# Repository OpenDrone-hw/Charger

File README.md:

# Charger

A distributed USB-C charging system for FPV battery packs. Two boards sharing
one charge, sense and balance core: a headless **charger node** that lives with
the pack, and a **manager** hub with a display and an encoder that drives
several nodes. No design exists yet; this page is the specification. If you
want to design it, say so on [Discord](https://discord.gg/v3sWmTcx3R).

## Why

Field charging is one parallel board, one power supply and a lot of trust. The
distributed shape puts the charge controller with the pack instead: each node
does its own constant-current, constant-voltage and balancing, and the manager
becomes a user interface and a power budget rather than the thing doing the
charging. A failure is then one pack rather than the whole board.

USB-C PD is the input because it is the supply people already carry.

## Specifications

Targets, not measurements. The site imports this table once a board exists.

| | |
|---|---|
| Charger node | Headless, 2S to 6S, one per pack |
| Manager | 2S to 8S, display and encoder, drives several nodes |
| Input | USB-C PD |
| Charge controller | TI BQ25758 buck-boost, or a justified alternative |
| Balancing | Per cell |
| Chemistries | LiPo, LiHV, Li-ion, LiFe |

## Constraints

- Two boards, one shared charge, sense and balance core.
- USB-C PD input on both boards; the manager may add other inputs.
- Assembly house chosen per release. LCSC basic parts preferred. Fab-ready manufacturing files are kept in a private Incutec production repository and are not published.
- Project-local KiCad libraries only, on the org template.
- Safety first: pack fault, thermal event and mid-charge disconnect are
  designed before the UI is.

## Prior art

An earlier schematic pass (BQ25758 core, TLA2528 cell ADC, TCA9554A driving
per-cell bleed FETs, ESP32 modules for ESP-NOW between manager and nodes) was
reviewed as not functional and removed from `main` on 2026-08-13. It is
reference for the thinking, not a design to continue from: tag
`pre-reset-2026-08-13`.

## Design questions

Open questions for the design:

- How the manager and nodes talk: wired bus, and which one? This decides
  the connector and half the enclosure. The earlier pass assumed ESP-NOW.
- Power budget: how is a fixed USB-C PD budget divided across nodes that
  each want it, and who decides?
- Cell count split: the node is 2S-6S and the manager 2S-8S. Is that split
  right, or should they match?
- Safety: what happens on a pack fault, a thermal event, or a disconnect
  mid-charge. This is the only product in the line that can start a fire on
  purpose.
- Enclosure: mechanical is as much of this product as the PCB.

## In the line

What pairs with what, and what is available:
[opendrone.be](https://opendrone.be).

## Contributing

KiCad files cannot be merged, so say what you intend to change before you do,
on [Discord](https://discord.gg/v3sWmTcx3R). How everything works:
[CONTRIBUTING.md](CONTRIBUTING.md).

## License

Hardware licensed under [CERN-OHL-S-2.0](https://ohwr.org/cern_ohl_s_v2.txt),
see [LICENSE](LICENSE).

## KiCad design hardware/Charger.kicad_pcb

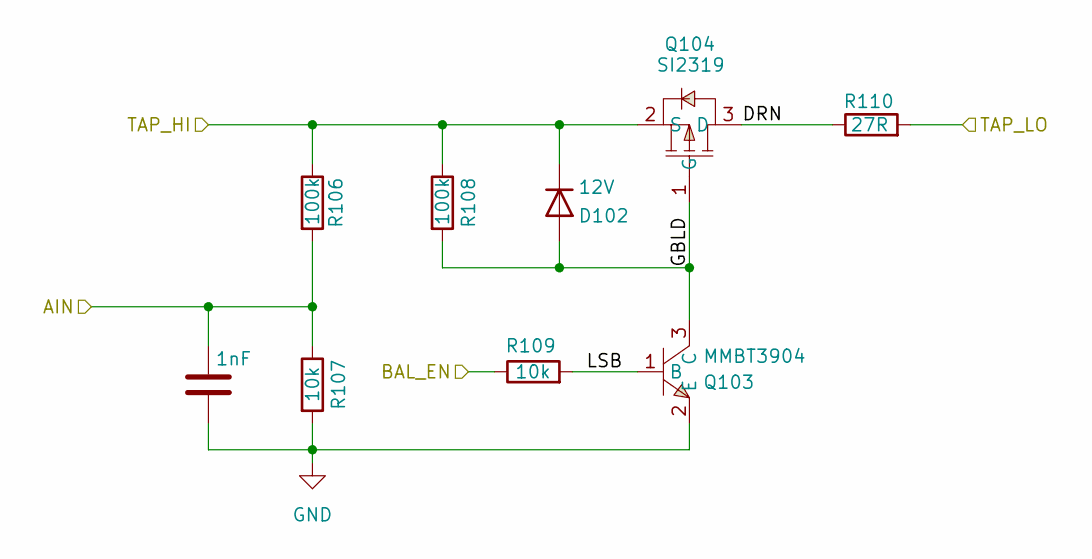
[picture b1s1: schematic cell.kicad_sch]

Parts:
C102: 1nF; C_0402_1005Metric; MPN GRM1555C1H102JA01D; LCSC C76947
D102: 12V; D_SOD-123; MPN MMSZ5242BT1G; LCSC C82050
Q103: MMBT3904; SOT-23; MPN MMBT3904; LCSC C20526
Q104: SI2319; SOT-23; MPN SI2319CDS-JSM; LCSC C18191323
R106: 100k; R_0402_1005Metric; MPN RT0402BRD07100KL; LCSC C852472
R107: 10k; R_0402_1005Metric; MPN RT0402BRD0710KL; LCSC C190095
R108: 100k; R_0402_1005Metric; MPN 0402WGF1003TCE; LCSC C25741
R109: 10k; R_0402_1005Metric; MPN 0402WGF1002TCE; LCSC C25744
R110: 27R; R_2512_6332Metric; MPN RC2512FK-7W27RL; LCSC C7337013

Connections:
/cell1/DRN: Q104.3 (D), R110.1
/cell1/GBLD: D102.2 (A), Q103.3 (C), Q104.1 (G), R108.2
/cell1/LSB: Q103.1 (B), R109.2
AIN1: C102.1, R106.2, R107.1; also elsewhere on the board
BAL_EN1: R109.1; also elsewhere on the board
GND: C102.2, Q103.2 (E), R107.2, R110.2; also elsewhere on the board
TAP1: D102.1 (K), Q104.2 (S), R106.1, R108.1; also elsewhere on the board

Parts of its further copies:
C103, C104, C105, C106, C107: 1nF; C_0402_1005Metric; MPN GRM1555C1H102JA01D; LCSC C76947
D103, D104, D105, D106, D107: 12V; D_SOD-123; MPN MMSZ5242BT1G; LCSC C82050
Q105, Q107, Q109, Q111, Q113: MMBT3904; SOT-23; MPN MMBT3904; LCSC C20526
Q106, Q108, Q110, Q112, Q114: SI2319; SOT-23; MPN SI2319CDS-JSM; LCSC C18191323
R111, R116, R121, R126, R131: 100k; R_0402_1005Metric; MPN RT0402BRD07100KL; LCSC C852472
R112, R117, R122, R127, R132: 10k; R_0402_1005Metric; MPN RT0402BRD0710KL; LCSC C190095
R113, R118, R123, R128, R133: 100k; R_0402_1005Metric; MPN 0402WGF1003TCE; LCSC C25741
R114, R119, R124, R129, R134: 10k; R_0402_1005Metric; MPN 0402WGF1002TCE; LCSC C25744
R115, R120, R125, R130, R135: 27R; R_2512_6332Metric; MPN RC2512FK-7W27RL; LCSC C7337013

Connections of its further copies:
/cell2/DRN: Q106.3 (D), R115.1
/cell2/GBLD: D103.2 (A), Q105.3 (C), Q106.1 (G), R113.2
/cell2/LSB: Q105.1 (B), R114.2
/cell3/DRN: Q108.3 (D), R120.1
/cell3/GBLD: D104.2 (A), Q107.3 (C), Q108.1 (G), R118.2
/cell3/LSB: Q107.1 (B), R119.2
/cell4/DRN: Q110.3 (D), R125.1
/cell4/GBLD: D105.2 (A), Q109.3 (C), Q110.1 (G), R123.2
/cell4/LSB: Q109.1 (B), R124.2
/cell5/DRN: Q112.3 (D), R130.1
/cell5/GBLD: D106.2 (A), Q111.3 (C), Q112.1 (G), R128.2
/cell5/LSB: Q111.1 (B), R129.2
/cell6/DRN: Q114.3 (D), R135.1
/cell6/GBLD: D107.2 (A), Q113.3 (C), Q114.1 (G), R133.2
/cell6/LSB: Q113.1 (B), R134.2
AIN2: C103.1, R111.2, R112.1; also elsewhere on the board
AIN3: C104.1, R116.2, R117.1; also elsewhere on the board
AIN4: C105.1, R121.2, R122.1; also elsewhere on the board
AIN5: C106.1, R126.2, R127.1; also elsewhere on the board
AIN6: C107.1, R131.2, R132.1; also elsewhere on the board
BAL_EN2: R114.1; also elsewhere on the board
BAL_EN3: R119.1; also elsewhere on the board
BAL_EN4: R124.1; also elsewhere on the board
BAL_EN5: R129.1; also elsewhere on the board
BAL_EN6: R134.1; also elsewhere on the board
GND: C103.2, C104.2, C105.2, C106.2, C107.2, Q105.2 (E), Q107.2 (E), Q109.2 (E), Q111.2 (E), Q113.2 (E), R112.2, R117.2, R122.2, R127.2, R132.2; also elsewhere on the board
TAP1: R115.2; also elsewhere on the board
TAP2: D103.1 (K), Q106.2 (S), R111.1, R113.1, R120.2; also elsewhere on the board
TAP3: D104.1 (K), Q108.2 (S), R116.1, R118.1, R125.2; also elsewhere on the board
TAP4: D105.1 (K), Q110.2 (S), R121.1, R123.1, R130.2; also elsewhere on the board
TAP5: D106.1 (K), Q112.2 (S), R126.1, R128.1, R135.2; also elsewhere on the board
TAP6: D107.1 (K), Q114.2 (S), R131.1, R133.1; also elsewhere on the board

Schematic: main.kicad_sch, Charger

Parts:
C1, C32, C33, C34, C41: 1uF; C_0402_1005Metric; MPN CL05A105KA5NQNC; LCSC C52923
C3, C4, C22, C23, C24, C25, C38, C40: 100nF; C_0402_1005Metric; MPN CL05B104KO5NNNC; LCSC C1525
C6: 4.7uF; C_0805_2012Metric; MPN CL21A475KAQNNNE; LCSC C23130
C20, C21: 470nF; C_0402_1005Metric; MPN CC0402KRX7R7BB474; LCSC C1546
C35: 10uF/50V; C_1210_3225Metric; MPN CS3225X7R106K500NRL; LCSC C2918502
C36, C37: 10uF/25V; C_0805_2012Metric; MPN CL21A106KAYNNNE; LCSC C15850
C39: 22uF; C_0805_2012Metric; MPN CL21A226MAQNNNE; LCSC C45783
C42: 0.1uF; C_0402_1005Metric; MPN CL05B104KO5NNNC; LCSC C131394
D2: USBLC6-2SC6; SOT-23-6_L2.9-W1.6-P0.95-LS2.8-BL; MPN USBLC6-2SC6; LCSC C2687116
D3: SMBJ30A; SMB_L4.6-W3.6-LS5.3-RD; MPN SMBJ30A; LCSC C113998
D4: SS56 60V 5A; D_SMA; MPN SS56; LCSC C65009
D5, D11: 12V Zener; SOD-123_L2.8-W1.8-LS3.7-RD; MPN MMSZ5242BT1G; LCSC C82050
D12: SMBJ28A; SMB_L4.6-W3.6-LS5.3-RD; MPN SMBJ28A; LCSC C2848703
F1: 5A fuse; R_1206_3216Metric; MPN 0466005.NRHF; LCSC C57525
J1: XT60 male; CONN-TH_XT60PW-M; MPN XT60PW-M; LCSC C98732
J2: Header 1x6; HDR-TH_6P-P2.54-V-M-1; MPN Header-Male-2.54_1x6; LCSC C37208
J3: USB-C; USB-C_SMD-TYPE-C-31-M-12_1; MPN TYPE-C-31-M-12; LCSC C165948
J4: XT60 female; TH_2P-XT60PW-F; MPN XT60PW-F; LCSC C428722
J5: XH-7; CONN-TH_7P-P2.50_B7B-XH-A-LF-SN; MPN B7B-XH-A; LCSC C144398
L1: 10uH; IND-SMD_L7.2-W6.6_GPSR0730; MPN SRP6540-100M; LCSC C780191
L2: 12uH; IND-SMD_L4.0-W4.0_FNR40XXS; MPN FNR5040S120MT; LCSC C167968
Q1: SI2319 40V P-FET; SOT-23-3_L2.9-W1.6-P1.90-LS2.8-BR; MPN SI2319CDS-JSM; LCSC C18191323
Q2, Q3, Q4, Q5: 40N06D 60V; PDFN3333-8_L3.1-W3.2-P0.65-LS3.4-BL_1; MPN 40N06D; LCSC C7543836
Q18: AP40P04G 40V P-FET; PDFN-8_L5.8-W4.9-P1.27-LS6.1-BL-A; MPN AP40P04G; LCSC C5443713
Q19: MMBT3906; SOT-23-3_L2.9-W1.6-P1.90-LS2.8-BR; MPN MMBT3906; LCSC C2891809
Q20, Q22: MMBT3904; SOT-23-3_L2.9-W1.6-P1.90-LS2.8-BR; MPN MMBT3904; LCSC C20526
Q21: BSS84; SOT-23-3_L2.9-W1.6-P1.90-LS2.8-BR; MPN BSS84; LCSC C85202
R2, R5, R48, R49, R52, R55, R63: 100k; R_0402_1005Metric; MPN 0402WGF1003TCE; LCSC C25741
R3, R4: 5mR; R_1206_3216Metric; MPN HoLLR1206-1W-5mR; LCSC C2988648
R7: 16.5k; R_0402_1005Metric; MPN FRC0402F1652TS; LCSC C3013155
R8: 4.02k; R_0402_1005Metric; MPN 0402WGF4021TCE; LCSC C43251
R9, R10, R11, R12: 10R; R_0402_1005Metric; MPN 0402WGF100JTCE; LCSC C25076
R13: 30.1k; R_0402_1005Metric; MPN 0402WGF3012TCE; LCSC C25803
R14, R16: 3.0k; R_0402_1005Metric; MPN 0402WGF3001TCE; LCSC C25784
R15, R66: 1M; R_0402_1005Metric; MPN 0402WGF1004TCE; LCSC C26083
R28, R29: 4.7k; R_0402_1005Metric; MPN 0402WGF4701TCE; LCSC C25900
R50: 93.1k; R_0402_1005Metric; MPN 0402WGF9312TCE; LCSC C25925
R51, R53, R54, R57, R58, R59, R60, R62, R64, R65, R67: 10k; R_0402_1005Metric; MPN 0402WGF1002TCE; LCSC C25744
R56: 43.2k; R_0402_1005Metric; MPN 0402WGF4322TCE; LCSC C25901
R61: 470R; R_0402_1005Metric; MPN 0402WGF4700TCE; LCSC C25117
RT1, RT2: 10k NTC; R_0402_1005Metric; MPN NCP15XH103F03RC; LCSC C77131
SW1: SW; SW-SMD_4P-L5.1-W5.1-P3.70-LS6.5-TL_H1.5; MPN TS-1187A-B-A-B; LCSC C318884
U1: HUSB238A; QFN-16_L3.0-W3.0-P0.50-BL-EP1.7; MPN HUSB238A-BB001-QN16R; LCSC C24833806
U2: BQ25758RRVR; QFN-36_L6.0-W5.0-P0.50-BL-EP-1; MPN BQ25758RRVR; LCSC C33222334
U3: TLA2528; WQFN-16_L3.0-W3.0-P0.50-TL-EP1.7; MPN TLA2528IRTER; LCSC C2866175
U4: TCA9554APWR; TSSOP-16_L5.0-W4.4-P0.65-LS6.4-BL; MPN TCA9554APWR; LCSC C477924
U5: TL432; SOT-23-3_L2.9-W1.6-P1.90-LS2.8-BR; MPN TL432AIDBZR; LCSC C82720
U6: LMV331; SOT-23-5_L3.0-W1.7-P0.95-LS2.8-BL; MPN LMV331IDBVR; LCSC C34731
U7: TPS560430X; SOT-23-6_L2.9-W1.6-P0.95-LS2.8-BL; MPN TPS560430XDBVR-MS; LCSC C50385346
U8: ESP32-C3-MINI-1-N4; WIFIM-SMD_ESP32-C3-MINI-1; MPN ESP32-C3-MINI-1-N4; LCSC C2838502

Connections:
+3.3V: C36.1, C37.1, L2.2, R55.1, U1.5 (VDD)
+VBAT: R4.2, R12.2, U2.12 (VO_SNS)
/main/3V3: C32.1, C34.1, C39.1, C40.1, J2.4, Q21.2 (S), R28.1, R29.1, R49.1, R52.1, R53.1, R54.1, R57.1, R58.1, R59.1, R60.1, R61.1, R63.1, U3.7 (AVDD), U3.10 (DVDD), U4.16 (VCC), U6.5, U8.3 (3V3)
/main/ACN_F: C21.2, C25.1, R10.2, U2.29 (ACN)
/main/ACOV: R14.1, R15.2
/main/ACP_F: C21.1, C24.1, R9.2, U2.30 (ACP)
/main/ACUV: R13.1, R14.2
/main/CE: Q21.3 (D), R52.2, U2.7 (~CE), U8.16 (IO10)
/main/CE_PG: Q20.3 (C), Q21.1 (G), R63.2
/main/DECAP: C33.1, U3.8 (DECAP)
/main/EN_ESP: C41.1, J2.5, R57.2, U8.8 (EN)
/main/HVDCP_DIS: U1.7 (EN_HVDCP/OUT1); also elsewhere on the board
/main/INT_CHG: U2.3 (~INT), U8.20 (IO6)
/main/IO9_BOOT: J2.6, R60.2, SW1.1 (A), SW1.3 (C), U8.23 (IO9)
/main/NTC_BOARD: R53.2, R54.2, RT2.1, U8.13 (IO1)
/main/OVCE_B: Q20.1 (B), R62.2
/main/OVCUT_PNPB: Q19.1 (B), Q22.3 (C), R65.2
/main/OVCUT_REV: D11.2 (A), Q18.4 (G), Q19.3 (C), R48.1
/main/OVLS_B: Q22.1 (B), R64.2
/main/OV_OUT: R49.2, R62.1, R64.1, U6.4
/main/OV_REF: R61.2, U5.1 (REF), U5.2 (CAT), U6.3
/main/OV_SENSE: C42.1, R50.2, R51.1, U6.1
/main/PACK_FUSED: F1.2, Q18.5 (D), Q18.6 (D), Q18.7 (D), Q18.8 (D), Q18.9 (D)
/main/PD_ADDR: R66.1, U1.8 (ADDR/ORIENT)
/main/PG_CHG: U2.6 (~PG), U8.21 (IO7)
/main/REGN: R67.1; also elsewhere on the board
/main/RX: J2.2, U8.30 (RXD0)
/main/SCL: R28.2, U1.10 (SCL/SNK_ISET), U2.1 (SCL), U3.13 (SCL), U4.14 (SCL), U8.19 (IO5)
/main/SDA: R29.2, U1.9 (SDA/SNK_VSET), U2.2 (SDA), U3.14 (SDA), U4.15 (SDA), U8.18 (IO4)
/main/SRN: C20.2, C23.1, R12.1, U2.13 (SRN)
/main/SRP: C20.1, C22.1, R11.2, U2.14 (SRP)
/main/STAT_CHG: U2.4 (STAT), U8.6 (IO3)
/main/STRAP_IO2: R58.2, U8.5 (IO2)
/main/STRAP_IO8: R59.2, U8.22 (IO8)
/main/SW1: C3.2, L1.1, Q2.1 (S), Q2.2 (S), Q2.3 (S), Q3.5 (D), U2.28 (SW1)
/main/SW2: C4.2, L1.2, Q4.1 (S), Q4.2 (S), Q4.3 (S), Q5.5 (D), U2.18 (SW2)
/main/TS: R67.2, RT1.1
/main/TX: J2.1, U8.31 (TXD0)
/main/USBC_CC1: J3.A5 (CC1), U1.3 (CC1)
/main/USBC_CC2: J3.B5 (CC2), U1.4 (CC2)
/main/USBC_DN: D2.3 (I/O2), D2.4 (I/O2), J3.A7 (DN1), J3.B7 (DN2), U1.2 (D-)
/main/USBC_DP: D2.1 (I/O1), D2.6 (I/O1), J3.A6 (DP1), J3.B6 (DP2), U1.1 (D+)
/main/USBC_VBUS: D2.5 (VBUS), D5.1 (K), J3.A4B9 (VBUS), J3.B4A9 (VBUS), Q1.2 (S), R2.2, U1.16 (VBUS)
/main/VBAT: D11.1 (K), Q18.1 (S), Q18.2 (S), Q18.3 (S), Q19.2 (E), R50.1, R65.1; also elsewhere on the board
/main/VBATX: Q4.5 (D), R4.1, R11.1; also elsewhere on the board
/main/VREG_BQ: C6.1, U2.23 (DRV_SUP), U2.24 (REGN)
/main/XT60IN: D4.2 (A), J1.2 (+)
AIN1: U3.15 (AIN0/GPIO0); also elsewhere on the board
AIN2: U3.16 (AIN1/GPIO1); also elsewhere on the board
AIN3: U3.1 (AIN2/GPIO2); also elsewhere on the board
AIN4: U3.2 (AIN3/GPIO3); also elsewhere on the board
AIN5: U3.3 (AIN4/GPIO4); also elsewhere on the board
AIN6: U3.4 (AIN5/GPIO5); also elsewhere on the board
BAL_EN1: U4.4 (PO); also elsewhere on the board
BAL_EN2: U4.5 (P1); also elsewhere on the board
BAL_EN3: U4.6 (P2); also elsewhere on the board
BAL_EN4: U4.7 (P3); also elsewhere on the board
BAL_EN5: U4.9 (P4); also elsewhere on the board
BAL_EN6: U4.10 (P5); also elsewhere on the board
GND: C1.2, C6.2, C22.2, C23.2, C24.2, C25.2, C32.2, C33.2, C34.2, C35.2, C36.2, C37.2, C39.2, C40.2, C41.2, C42.2, D2.2 (GND), D3.2 (A), D12.2 (A), J1.1 (-), J1.3, J1.4, J2.3, J3.1 (EH), J3.2 (EH), J3.3 (EH), J3.4 (EH), J3.A1B12 (GND), J3.B1A12 (GND), J4.2, J4.4 (-), J5.1, Q3.1 (S), Q3.2 (S), Q3.3 (S), Q5.1 (S), Q5.2 (S), Q5.3 (S), Q20.2 (E), Q22.2 (E), R5.2, R7.2, R8.2, R13.2, R16.1, R48.2, R51.2, R56.2, R66.2, RT1.2, RT2.2, SW1.2 (B), SW1.4 (D), U1.12 (EN_N), U1.17 (GND), U2.22 (PGND), U2.35 (ACOV), U2.37 (PGND), U3.5 (AIN6/GPIO6), U3.6 (AIN7/GPIO7), U3.9 (GND), U3.17 (GND), U4.1 (AO), U4.2 (A1), U4.3 (A2), U4.8 (GND), U5.3 (AN), U6.2, U7.2 (GND), U8.1 (GND), U8.2 (GND), U8.11 (GND), U8.14 (GND), U8.36 (GND), U8.37 (GND), U8.38 (GND), U8.39 (GND), U8.40 (GND), U8.41 (GND), U8.42 (GND), U8.43 (GND), U8.44 (GND), U8.45 (GND), U8.46 (GND), U8.47 (GND), U8.48 (GND), U8.49 (GND), U8.50 (GND), U8.51 (GND), U8.52 (GND), U8.53 (GND); also elsewhere on the board
unnamed 78: Q2.5 (D), R3.2, R10.1; also elsewhere on the board
unnamed: Q2.4 (G), U2.27 (HIDRV1)
unnamed: Q3.4 (G), U2.25 (LODRV1)
unnamed: Q4.4 (G), U2.19 (HIDRV2)
unnamed: Q5.4 (G), U2.21 (LODRV2)
unnamed: C3.1, U2.26 (BTST1)
unnamed: C4.1, U2.20 (BTST2)
unnamed: R5.1, U2.36 (FSW_SYNC)
unnamed: R8.1, U2.10 (IIN)
unnamed: R7.1, U2.9 (IOUT)
unnamed: R16.2, U2.17 (MODE)
unnamed: C38.1, U7.1 (CB)
unnamed: R55.2, R56.1, U7.3 (FB)
unnamed: C38.2, L2.1, U7.6 (SW)
TAP1: J5.2; also elsewhere on the board
TAP2: J5.3; also elsewhere on the board
TAP3: J5.4; also elsewhere on the board
TAP4: J5.5; also elsewhere on the board
TAP5: J5.6; also elsewhere on the board
TAP6: D12.1 (K), F1.1, J4.1, J4.3 (+), J5.7; also elsewhere on the board

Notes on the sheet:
==== POWER ====
==== BMS ====
USB-C PORT
OR XT60 DC IN
ESD PROTECTION
==== MCU ====
PD TRIGGER DC IN

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
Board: 2 copper layers, 164 parts (0 on the bottom side), 101 nets, no tracks yet.

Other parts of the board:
C2, C7: 1uF; C_0402_1005Metric
C5: 4.7uF; C_0805_2012Metric
C8, C9, C10, C11, C12, C13, C14, C15: 10uF/50V; C_1210_3225Metric
C16, C17, C18, C19, C26, C27: 100uF/63V; CAP-SMD_BD6.3-L6.6-W6.6-FD
R1: 910k; R_0402_1005Metric

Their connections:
/main/HVDCP_DIS: R1.1; also elsewhere on the board
/main/REGN: C5.1; also elsewhere on the board
/main/VBAT: C12.1, C13.1, C14.1, C15.1, C18.1, C19.1; also elsewhere on the board
/main/VBATX: C8.1, C9.1, C10.1, C11.1, C16.1, C17.1, C27.1; also elsewhere on the board
GND: C2.2, C5.2, C7.2, C8.2, C9.2, C10.2, C11.2, C12.2, C13.2, C14.2, C15.2, C16.2, C17.2, C18.2, C19.2, C26.2, C27.2, R1.2; also elsewhere on the board
unnamed 78: C26.1; also elsewhere on the board

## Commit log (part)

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2026-06-14 README: correct power scope to <=3A / ~65W@6S (FPV)
